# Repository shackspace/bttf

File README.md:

BTTF Clock
==========

A triple wall clock modeled after the Time Circuits from a well-known SF movie of the 80s.

Designed by [Timm][1] and [Jocki][2] of [shackspace][3], together with and for our friends at [PCB-Pool][4].

Technology
==========

The clock is driven by an Arduino or a compatible uC board. It consists of two components:

 1. A shield for the Arduino which houses a battery-backed real-time clock (RTC) and combines Arduino pins and power into a bus.
 1. A display board representing a single clock, including numeric and alphanumeric LED displays, LEDs, LED drivers and brightness control.
    The display boards can be daisy-chained to an almost arbitrary amount. For a full triple clock, you'd use three of these, with differently colored LEDs.

Display Bus
-----------

The display bus consists of ground, two power rails and five logic signals. The two power rails are logic power and LED power -- both run at 5V, but the shield allows to separate them and power the LEDs from an external power supply while the logic including the Arduino is powered through USB. This is to prevent the external power supply from feeding into the USB or vice versa. Powering the whole clock from a PC USB port is usually not possible because the LEDs draw up to one Ampere and most hosts will disable the port as soon as the displays turn on.

The logic pins are what's needed to control a multiplexed display driven by a TLC59282 constant-current shift register towards ground, and a 74HC164 non-latching shift register power p-FETs towards 5V:

 * The TLC is controlled by the LATCH and BLANK signals, data is shifted in using the SDATA\_IN and SCLK signals. The SDATA\_OUT signal of one display connects to SDATA\_IN of the next display in the chain.
 * The shift register is clocked whenever the TLC is latched, so the LATCH signal can serve as its clock. In addition, we need a serial input !COL0 that is set to 0 (turning the p-FET on) on the first multiplex step and 1 (turning the p-FET off) on all other steps, so that we have a single "p-FET on" signal clocking through the shift register.

All signals but the SDATA_IN/OUT signals are connected in parallel across all display modules, the SDATA signals are daisy-chained from one module to the next -- as a result of this, each module has a distinct input and output connector.

Subdirectories
==============

[controller](controller) - The Arduino shield, designed in [Eagle][5], complete with BOM in CSV format.  
[display](display) - The display module, designed using [KiCad][6] because it exceeds Eagle's size limits, also with BOM.  
[firmware](firmware) - The full firmware, ready for upload using the Arduino IDE.

Setting up
==========

To complete the clock into a working thing (after soldering), you will need a battery, an Arduino (or compatible) and a 5V 1A power supply with the usual barrel plug (center positive). Put the battery into the holder, put the shield on the Arduino, connect it to the first display using a ribbon cable. The top connector on each display is the input, the bottom one is the output. Daisy-chain as many displays as you like - or have ;)

The power supply goes into the shield, not the Arduino. There's a jumper on the shield that connects the LED driver's power supply (fed through the barrel jack) and the logic power supply (including the Arduino)  leave that open if you have both the Arduino connected to the PC and the power supply hooked up to the shield, otherwise close it.

Upload the firmware to the Arduino and connect to it using the Serial Monitor at 9600 Baud. Send a "?" to the Arduino to get some help on how to set up the clock. Each display line can be set to display either a fixed value (any alphanumerical+numerical string, not just a valid time) or the current time as delivered by the battery-backed RTC. To make the RTC start ticking, you will have to set its time once. You can set each display's brightness using the trimmers on the back  you might even be able to power the thing via USB on lowest brightness, but no guarantees.

[1]: http://twitter.com/timmedia
[2]: http://twitter.com/dop3j0e
[3]: http://shackspace.de/
[4]: http://pcb-pool.com/
[5]: http://www.cadsoft.de/eagle-pcb-design-software/
[6]: http://www.kicad-pcb.org/

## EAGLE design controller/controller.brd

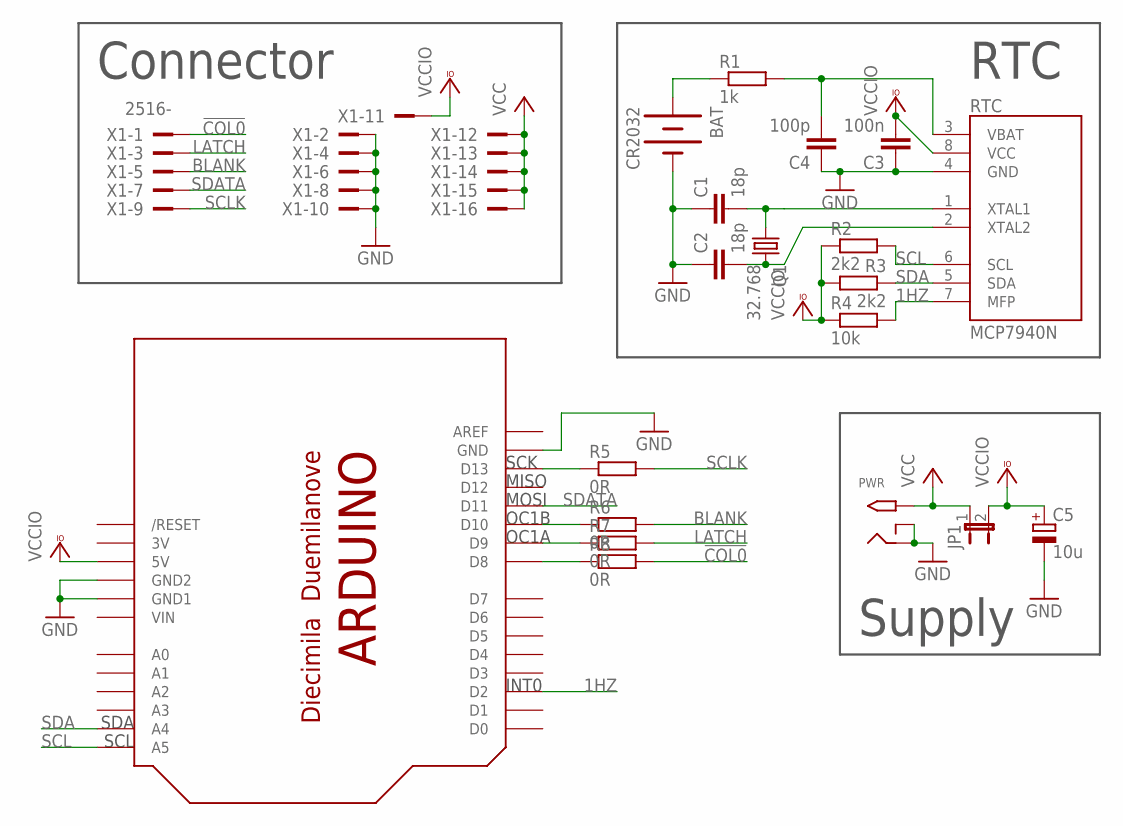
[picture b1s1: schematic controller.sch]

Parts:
ARDU: ARDUINODUEMILANOVE; ARDUINO
BAT: CR2032; HAR-S8421
C1, C2: 18p; C0603
C3: 100n; C0603K
C4: 100p; C0603
C5: 10u; C/6032-28R
JP1: JP1E; JP1
PWR: 2.1MMJACKTHM; PJ-102A
Q1: 32.768; MM20SS
R1: 1k; R0603
R2, R3: 2k2; R0603
R4: 10k; R0603
R5, R6, R7, R8: 0R; R0603
RTC: MCP7940N; SO08
X1: 2516-; PAK100/2500-16

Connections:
1HZ: ARDU.D2, R4.2, RTC.7 (MFP)
3V: ARDU.3V
!COL0: R8.2, X1.1
BLANK: R6.2, X1.5
GND: ARDU.GND, ARDU.GND1, ARDU.GND2, BAT.-, C1.1, C2.1, C3.1, C4.1, C5.-, PWR.RING, PWR.RING_SW, RTC.4 (GND), X1.2, X1.4, X1.6, X1.8, X1.10
LATCH: R7.2, X1.3
unnamed: C1.2, Q1.1, RTC.1 (XTAL1)
unnamed: C2.2, Q1.4 (2), RTC.2 (XTAL2)
unnamed: BAT.+, R1.1
unnamed: C4.2, R1.2, RTC.3 (VBAT)
unnamed: ARDU.D13, R5.1
unnamed: ARDU.D10, R6.1
unnamed: ARDU.D9, R7.1
unnamed: ARDU.D8, R8.1
SCL: ARDU.A5, R2.2, RTC.6 (SCL)
SCLK: R5.2, X1.9
SDA: ARDU.A4, R3.1, RTC.5 (SDA)
SDATA: ARDU.D11, X1.7
VCC: JP1.1, PWR.TIP, X1.12, X1.13, X1.14, X1.15, X1.16
VCCIO: ARDU.5V, C3.2, C5.+, JP1.2, R2.1, R3.2, R4.1, RTC.8 (VCC), X1.11
VIN: ARDU.VIN

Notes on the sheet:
Connector
RTC
Supply
SCK
MISO
MOSI
OC1B
OC1A
INT0
SDA
SCL

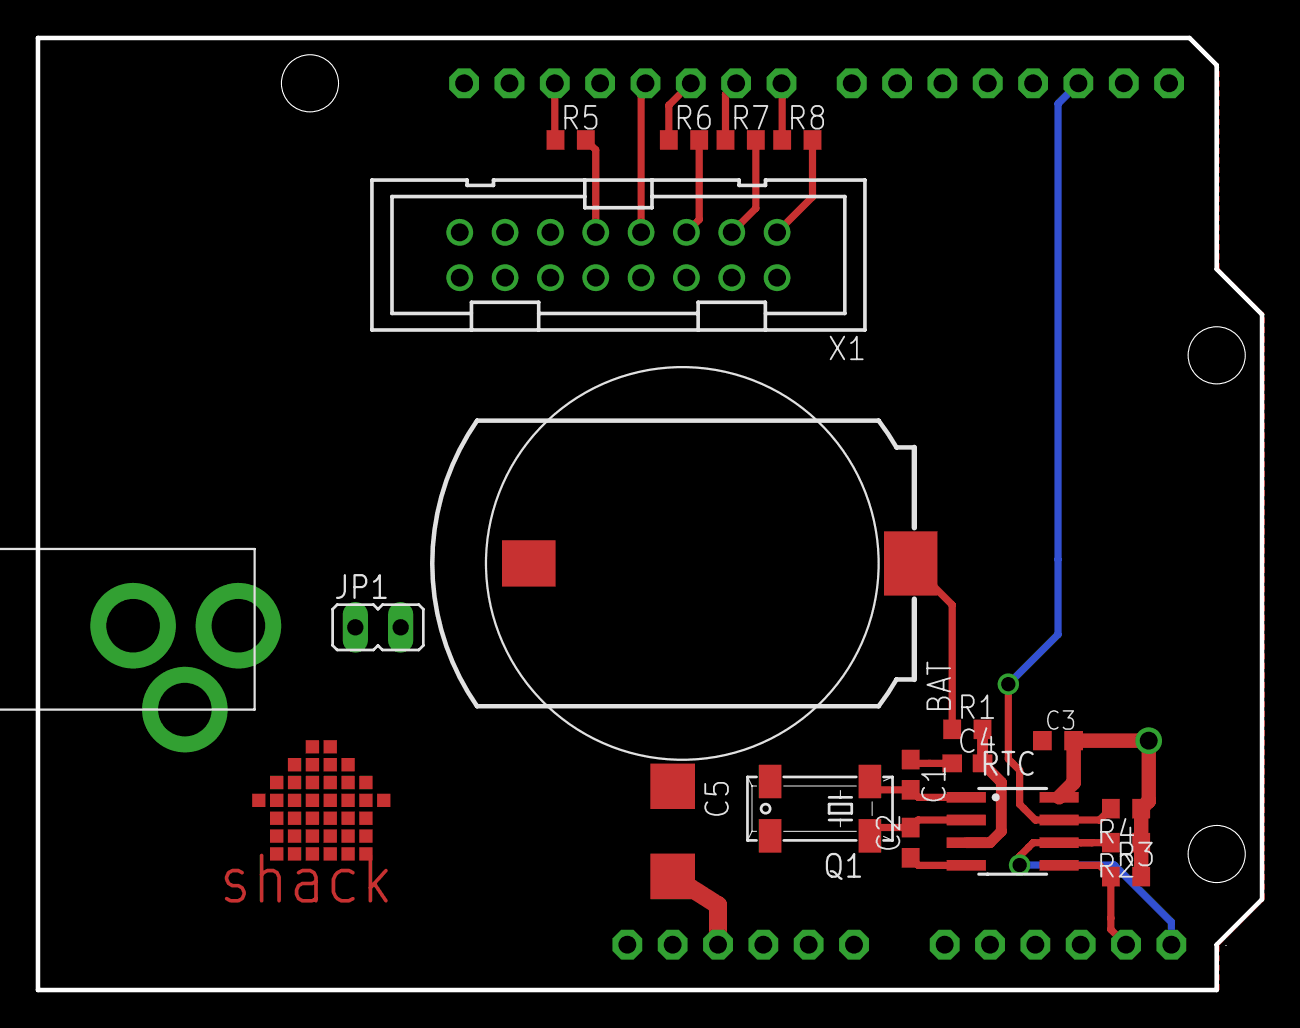
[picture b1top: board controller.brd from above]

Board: 2 copper layers, 68.6 x 53.3 mm, 20 parts (0 on the bottom side), 19 nets.

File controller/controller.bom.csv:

Part,Value,Device,Package,Description,Description2,Qty,Place_YES/NO,Povided_by_customer_YES/NO,Distributor,Ordernumber,Weblink,Remarks_customer,Unit_price,Total_price,REMARKS_BETA,OPTION1,OPTION2,OPTION3
BAT,CR2032,CR2032,HAR-S8421,CR2032 Battery Holder, ,1,yes,no,Digikey,952-1737-1-ND,http://www.digikey.de/scripts/DKSearch/dksus.dll?Detail&item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, , , , , , , 
"C1, C2",22p,C-EUC0603,C0603,"CAPACITOR, European symbol", ,2,no,no,, , , , , , , , , 
C3,100n,C-EUC0603K,C0603K,"CAPACITOR, European symbol", ,1,yes,no,Beta,6242480,http://de.rs-online.com/web/search/searchBrowseAction.html?m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, , , , , , , 
C4,100p,C-EUC0603,C0603,"CAPACITOR, European symbol", ,1,no,no,, , , , , , , , , 
C5,10u,CPOL-EUC/6032-28R,C/6032-28R,"POLARIZED CAPACITOR, European symbol","Tantalkondensator, 6032-28, 25V, 10µF",1,yes,no,Beta,4649306P,http://uk.rs-online.com/web/search/searchBrowseAction.html?m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, , , , , , , 
JP1, ,JP1E,JP1,JUMPER, ,1,no,no,, , , , , , , , , 
PWR,2.1MMJACKTHM,2.1MMJACKTHM,PJ-102A,2.1mm x 5.5mm THM DC jack with internal switch, ,1,yes,no,Digikey,CP-202A-ND,http://www.digikey.de/scripts/DKSearch/dksus.dll?Detail&item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, , , , , , , 
Q1,32.768kHz,CRYSTALMM20SS,MM20SS,CRYSTAL, ,1,yes,no,Digikey,631-1000-1-ND,http://www.digikey.de/scripts/DKSearch/dksus.dll?Detail&item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, , , , , , , 
R1,1k,R-EU_R0603,R0603,"RESISTOR, European symbol","RESISTOR, 0.1W, 1%",1,yes,no,Beta,6979246,http://uk.rs-online.com/web/search/searchBrowseAction.html?m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, , , , , , , 
"R2, R3",2k2,R-EU_R0603,R0603,"RESISTOR, European symbol","RESISTOR, 0.1W, 1%",2,yes,no,Beta,6979270,http://uk.rs-online.com/web/search/searchBrowseAction.html?m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, , , , , , , 
R4,10k,R-EU_R0603,R0603,"RESISTOR, European symbol","RESISTOR, 0.1W, 1%",1,yes,no,Beta,6979325,http://uk.rs-online.com/web/search/searchBrowseAction.html?m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, , , , , , , 
"R5, R6, R7, R8",0R,R-EU_R0603,R0603,"RESISTOR, European symbol", ,4,no,no,, , , , , , , , , 
RTC,MCP7940N,MCP7940N,SO08,Microchip MCP7940N RTC, ,1,yes,no,Digikey,MCP7940N-I/SN-ND,http://www.digikey.de/scripts/DKSearch/dksus.dll?Detail&item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, , , , , , , 
X1,,2516-,PAK100/2500-16,2x8 Wannensteckverbinder, ,1,yes,no,Digikey,S9171-ND,http://www.digikey.de/scripts/DKSearch/dksus.dll?Detail&item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, , , , , , , 
NOT ON BOARD,5V 2A,,,DC Power Supply,,1,no,,Digikey,T1150-P5P-ND,http://www.digikey.de/scripts/DKSearch/dksus.dll?Detail&item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,,,,,,,

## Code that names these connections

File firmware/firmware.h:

#ifndef FIRMWARE_H
#define FIRMWARE_H

#include <stdio.h>
#include <stdlib.h>
#include <stdint.h>
#include <avr/pgmspace.h>

#define NUM_DISPLAYS 3

#define LED_AM (1 << 4)
#define LED_PM (1 << 5)
#define LED_SEC1 (1 << 6)
#define LED_SEC2 (1 << 7)
#define LED_CATHODE (1 << 0)

#define bcd2dec(x) (((((x) >> 4) & 0xF) * 10) + ((x) & 0xF))

#define COL0_PIN 8
#define SECONDS_PIN 2

/* Don't change these, they correspond to OC1A and OC1B */
#define LATCH_PIN 9
#define BLANK_PIN 10

/* offsets in the digits array */
#define DAY 0
#define YEAR 2
#define HOUR 6
#define MINUTE 8

/* from main file */

void saveConfig();

/* from fonts.c */

extern const PROGMEM uint16_t font16['Z' - '0' + 1];
extern const PROGMEM uint16_t font7a[10];
extern const PROGMEM uint16_t font7b[10];

/* from rtc.cpp */

#define RTC_I2C_ADDRESS 0x6F

struct Time {
	uint8_t seconds, minutes, hours, day, month, year;
	bool pm;
};

extern Time rtc;

void setupRtc();
void loadRtcTime();
void setRtcTime(Time &time);

/* from display.cpp */

struct Display {
	bool useRtc;
	char month[3];
	uint8_t digits[10];
	uint8_t leds;
};

extern Display displays[NUM_DISPLAYS];

void setupDisplayDriver();
void setDisplay(Display *disp, Time &time);

/* from serial.cpp */

void checkCommand();

#endif

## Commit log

2014-11-29 Add schematic PDFs
2014-11-29 Add datasheets
2015-01-23 added license file
2015-01-23 added frontpanel image sources
